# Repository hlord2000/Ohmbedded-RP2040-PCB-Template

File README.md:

# Keyboard PCB Integration with Microcontrollers

This GitHub project provides guidance on integrating microcontrollers into keyboard PCBs. It focuses on the RP2040 microcontroller from the Raspberry Pi foundation, which offers several features such as a dual-core Arm Cortex-M0+ processor, multiple communication interfaces, and QMK/Via/Vial support.

## Schematic Capture

Before proceeding with board layout, it is important to understand the steps involved in schematic capture. The README provides an overview of the RP2040 microcontroller, including its integrated 3.3V->1.1V regulator, pin connections like TESTEN and RUN_, and the need for additional components such as decoupling capacitors.

## Power Supply and USB Bootloader

The RP2040 is powered through USB and features a built-in USB bootloader for easy programming. The README mentions the use of a 3.3V fixed regulator, USBLC6 ESD protection IC, PTC resettable fuse, and a ferrite bead for EMI suppression.

## PCB Connectors

The project includes information about the USB-C port, its orientation detection pins (CC1/CC2), and the 5.1k resistors used for USB power delivery. Additionally, a JST connector is introduced for use with a Unified Daughter Board.

## Crystal and External Flash

A crystal is employed to provide accurate timing for USB functionality. The README also covers the connections to the RP2040's external flash, including buttons for forcing the ROM bootloader and resetting the microcontroller.

## Indicator LED and Switch Matrix

An indicator LED example for caps lock indication is given, along with considerations for selecting an appropriate LED resistor value. The README highlights the use of diodes in the switch matrix to prevent "ghosting" and enable n-key rollover.

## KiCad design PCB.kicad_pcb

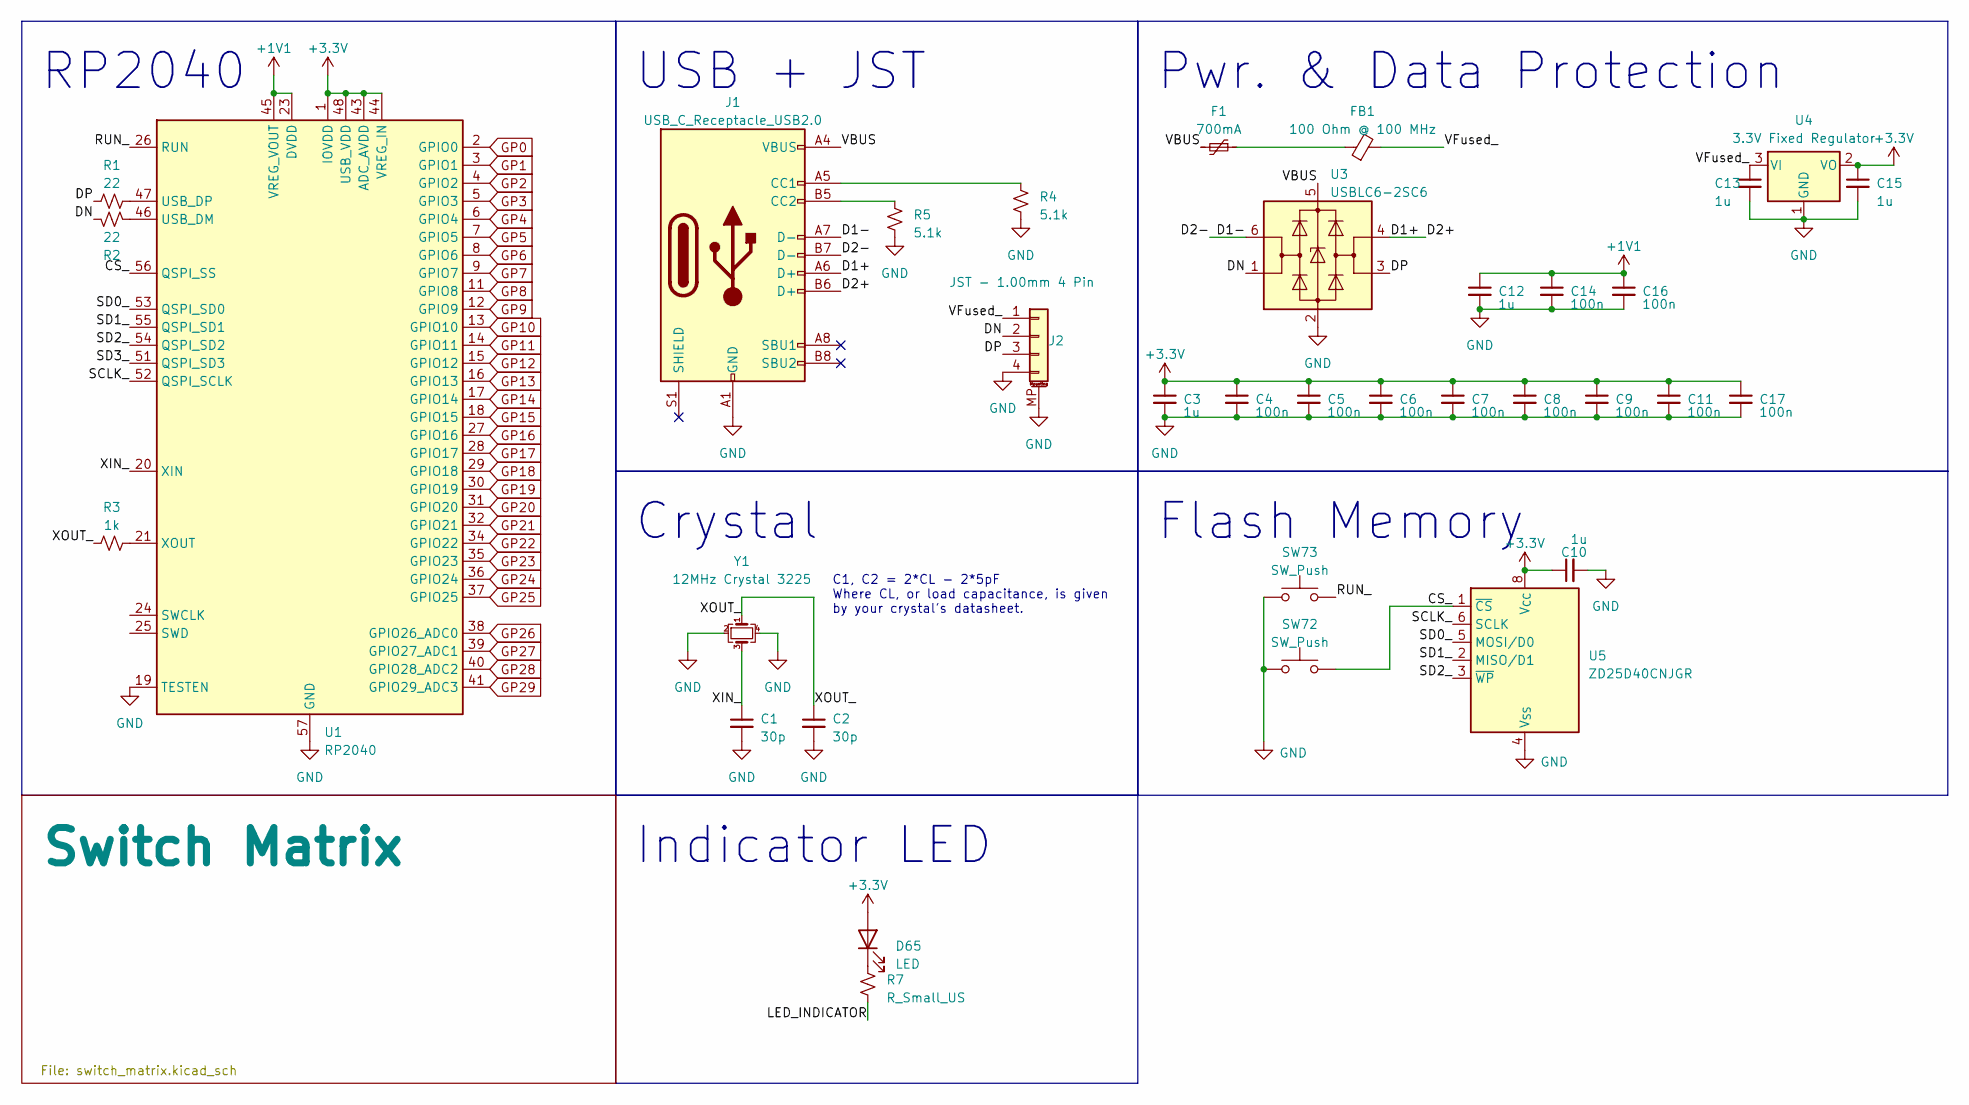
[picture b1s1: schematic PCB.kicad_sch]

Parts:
C1, C2: 30p; C_0402_1005Metric; LCSC C1562
C3, C10, C12, C13, C15: 1u; C_0402_1005Metric; LCSC C52923
C4, C5, C6, C7, C8, C9, C11, C14, C16, C17: 100n; C_0402_1005Metric; LCSC C1525
D65: LED; LED_MX_3mm
F1: 700mA; Fuse_0402_1005Metric; LCSC C914086
FB1: 100 Ohm @ 100 MHz; L_0402_1005Metric; LCSC C85812
J1: USB_C_Receptacle_USB2.0; USB_C_Receptacle_GCT_USB4085
J2: JST - 1.00mm 4 Pin; JST_SH_SM04B-SRSS-TB_1x04-1MP_P1.00mm_Horizontal; LCSC C160404
R1, R2: 22; R_0402_1005Metric; LCSC C25152
R3: 1k; R_0402_1005Metric; LCSC C106235
R4, R5: 5.1k; R_0402_1005Metric; LCSC C25905
R7: R_Small_US; R_0402_1005Metric
SW72, SW73: SW_Push; SW_SPST_SKQG_WithoutStem; LCSC C115351
U1: RP2040; QFN-56-1EP_7x7mm_P0.4mm_EP3.2x3.2mm_ThermalVias; LCSC C2040
U3: USBLC6-2SC6; SOT-23-6; LCSC C558442
U4: 3.3V Fixed Regulator; TSOT-23; LCSC C150715
U5: ZD25D40CNJGR; USON-8_1.5x1.5mm_P0.45mm; LCSC C3646778
Y1: 12MHz Crystal 3225; Crystal_SMD_3225-4Pin_3.2x2.5mm; LCSC C9002

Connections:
+1V1: C12.1, C14.1, C16.1, U1.23 (DVDD), U1.45 (VREG_VOUT), U1.50 (DVDD)
+3.3V: C3.1, C4.1, C5.1, C6.1, C7.1, C8.1, C9.1, C10.1, C11.1, C15.1, C17.1, D65.2 (A), U1.1 (IOVDD), U1.10 (IOVDD), U1.22 (IOVDD), U1.33 (IOVDD), U1.42 (IOVDD), U1.43 (ADC_AVDD), U1.44 (VREG_IN), U1.48 (USB_VDD), U1.49 (IOVDD), U4.2 (VO), U5.8 (V_{CC})
/CS_: SW72.2, U1.56 (QSPI_SS), U5.1 (~CS)
/D1+: J1.A6 (D+), J1.B6 (D+), U3.4 (I/O2)
/D1-: J1.A7 (D-), J1.B7 (D-), U3.6 (I/O1)
/DN: J2.2, R2.2, U3.1 (I/O1)
/DP: J2.3, R1.1, U3.3 (I/O2)
/LED_INDICATOR: R7.2
/RUN_: SW73.2, U1.26 (RUN)
/SCLK_: U1.52 (QSPI_SCLK), U5.6 (SCLK)
/SD0_: U1.53 (QSPI_SD0), U5.5 (MOSI/D0)
/SD1_: U1.55 (QSPI_SD1), U5.2 (MISO/D1)
/SD2_: U1.54 (QSPI_SD2), U5.3 (~WP)
/SD3_: U1.51 (QSPI_SD3)
/VBUS: F1.2, J1.A4 (VBUS), J1.A9 (VBUS), J1.B4 (VBUS), J1.B9 (VBUS), U3.5 (VBUS)
/VFused_: C13.1, FB1.2, J2.1, U4.3 (VI)
/XIN_: C1.1, U1.20 (XIN), Y1.3
/XOUT_: C2.1, R3.1, Y1.1
GND: C1.2, C2.2, C3.2, C4.2, C5.2, C6.2, C7.2, C8.2, C9.2, C10.2, C11.2, C12.2, C13.2, C14.2, C15.2, C16.2, C17.2, J1.A1 (GND), J1.A12 (GND), J1.B1 (GND), J1.B12 (GND), J2.4, J2.MP (MountPin), R4.1, R5.1, SW72.1, SW73.1, U1.19 (TESTEN), U1.57 (GND), U3.2 (GND), U4.1 (GND), U5.4 (V_{SS}), U5.9 (PAD/V_{SS}), Y1.2, Y1.4
GP0: U1.2 (GPIO0); also elsewhere on the board
GP1: U1.3 (GPIO1); also elsewhere on the board
GP2: U1.4 (GPIO2); also elsewhere on the board
GP3: U1.5 (GPIO3); also elsewhere on the board
GP4: U1.6 (GPIO4)
GP5: U1.7 (GPIO5)
GP6: U1.8 (GPIO6)
GP7: U1.9 (GPIO7)
GP8: U1.11 (GPIO8)
GP9: U1.12 (GPIO9)
GP10: U1.13 (GPIO10)
GP11: U1.14 (GPIO11)
GP12: U1.15 (GPIO12)
GP13: U1.16 (GPIO13)
GP14: U1.17 (GPIO14)
GP15: U1.18 (GPIO15)
GP16: U1.27 (GPIO16)
GP17: U1.28 (GPIO17)
GP18: U1.29 (GPIO18)
GP19: U1.30 (GPIO19)
GP20: U1.31 (GPIO20)
GP21: U1.32 (GPIO21)
GP22: U1.34 (GPIO22)
GP23: U1.35 (GPIO23)
GP24: U1.36 (GPIO24)
GP25: U1.37 (GPIO25)
GP26: U1.38 (GPIO26_ADC0)
GP27: U1.39 (GPIO27_ADC1)
GP28: U1.40 (GPIO28_ADC2)
GP29: U1.41 (GPIO29_ADC3)
unnamed: D65.1 (K), R7.1
unnamed: F1.1, FB1.1
unnamed: J1.A5 (CC1), R4.2
unnamed: J1.B5 (CC2), R5.2
unnamed: R2.1, U1.46 (USB_DM)
unnamed: R1.2, U1.47 (USB_DP)
unnamed: R3.2, U1.21 (XOUT)

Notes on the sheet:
Flash Memory
Pwr. & Data Protection
C1, C2 = 2*CL - 2*5pF Where CL, or load capacitance, is given by your crystal's datasheet.
Indicator LED
Crystal
RP2040
USB + JST

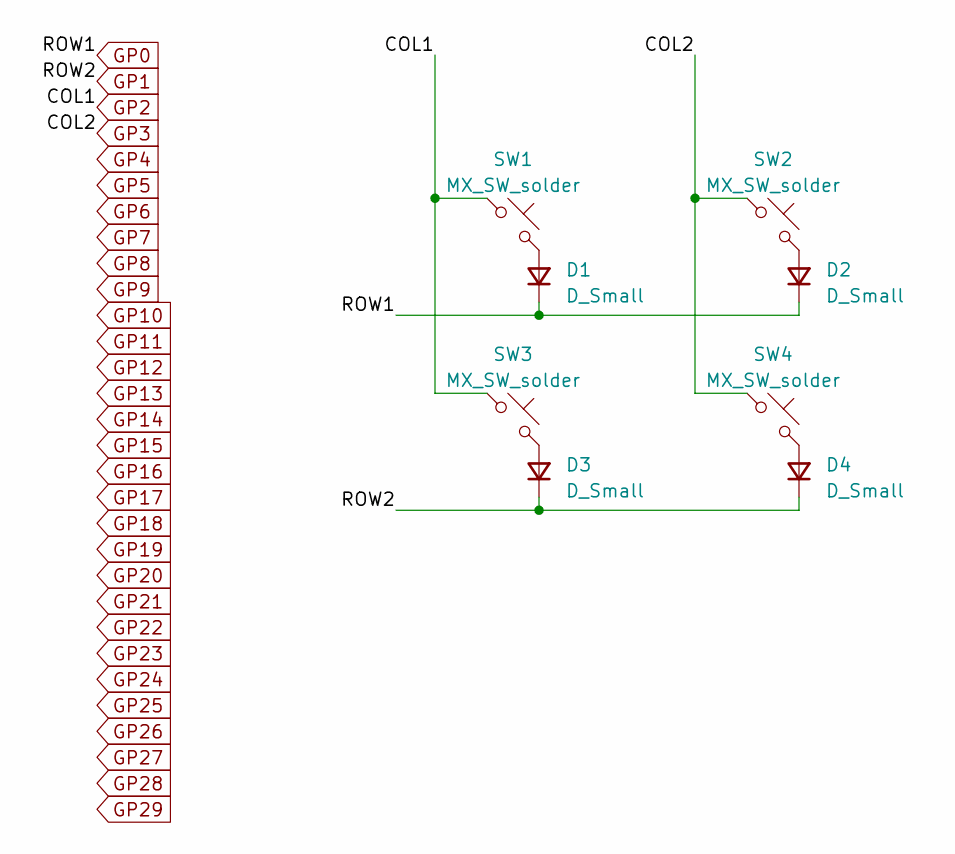
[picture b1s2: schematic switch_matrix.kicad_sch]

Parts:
D1, D2, D3, D4: D_Small; D_SOD-123; LCSC C81598
SW1, SW2, SW3, SW4: MX_SW_solder; SW_MX_1u

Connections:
GP0: D1.1 (K), D2.1 (K); also elsewhere on the board
GP1: D3.1 (K), D4.1 (K); also elsewhere on the board
GP2: SW1.1, SW3.1; also elsewhere on the board
GP3: SW2.1, SW4.1; also elsewhere on the board
unnamed: D1.2 (A), SW1.2
unnamed: D2.2 (A), SW2.2
unnamed: D3.2 (A), SW3.2
unnamed: D4.2 (A), SW4.2

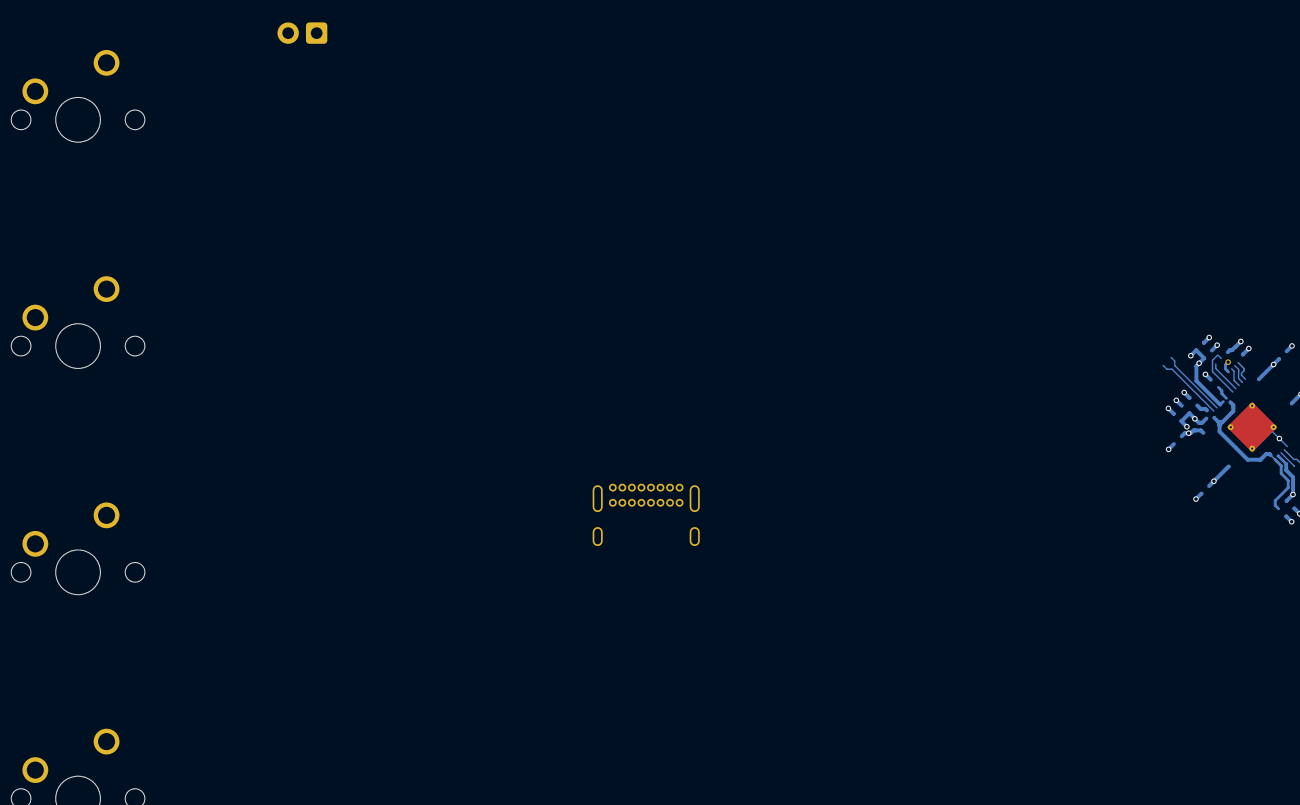
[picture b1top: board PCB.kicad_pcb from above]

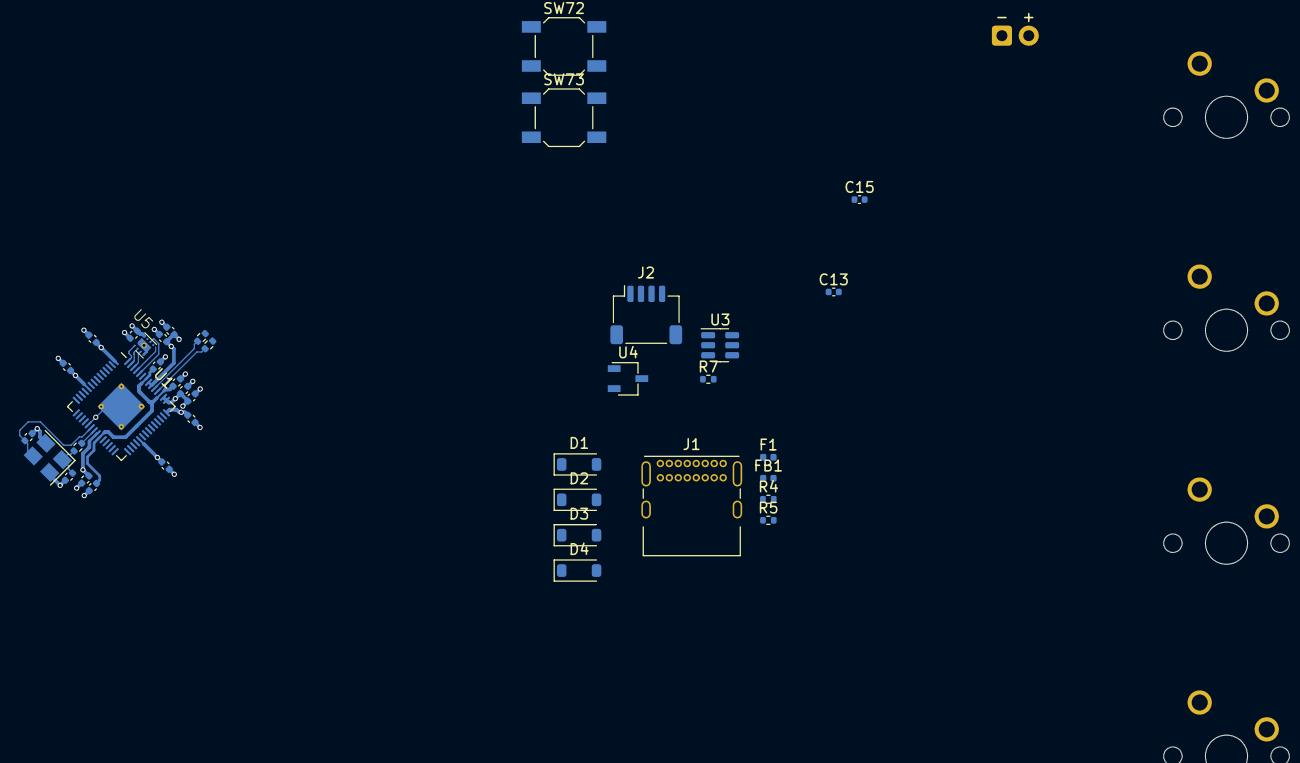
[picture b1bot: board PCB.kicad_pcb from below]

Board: 4 copper layers, 43 parts (38 on the bottom side), 32 nets.

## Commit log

2023-06-25 Initial commit.
2023-06-25 Updated readme and added image.
2023-06-26 Updated LCSC part numbers for all parts.
2023-07-16 Added missing decoupling capacitor and cr created example layout.
2025-03-25 Added license
